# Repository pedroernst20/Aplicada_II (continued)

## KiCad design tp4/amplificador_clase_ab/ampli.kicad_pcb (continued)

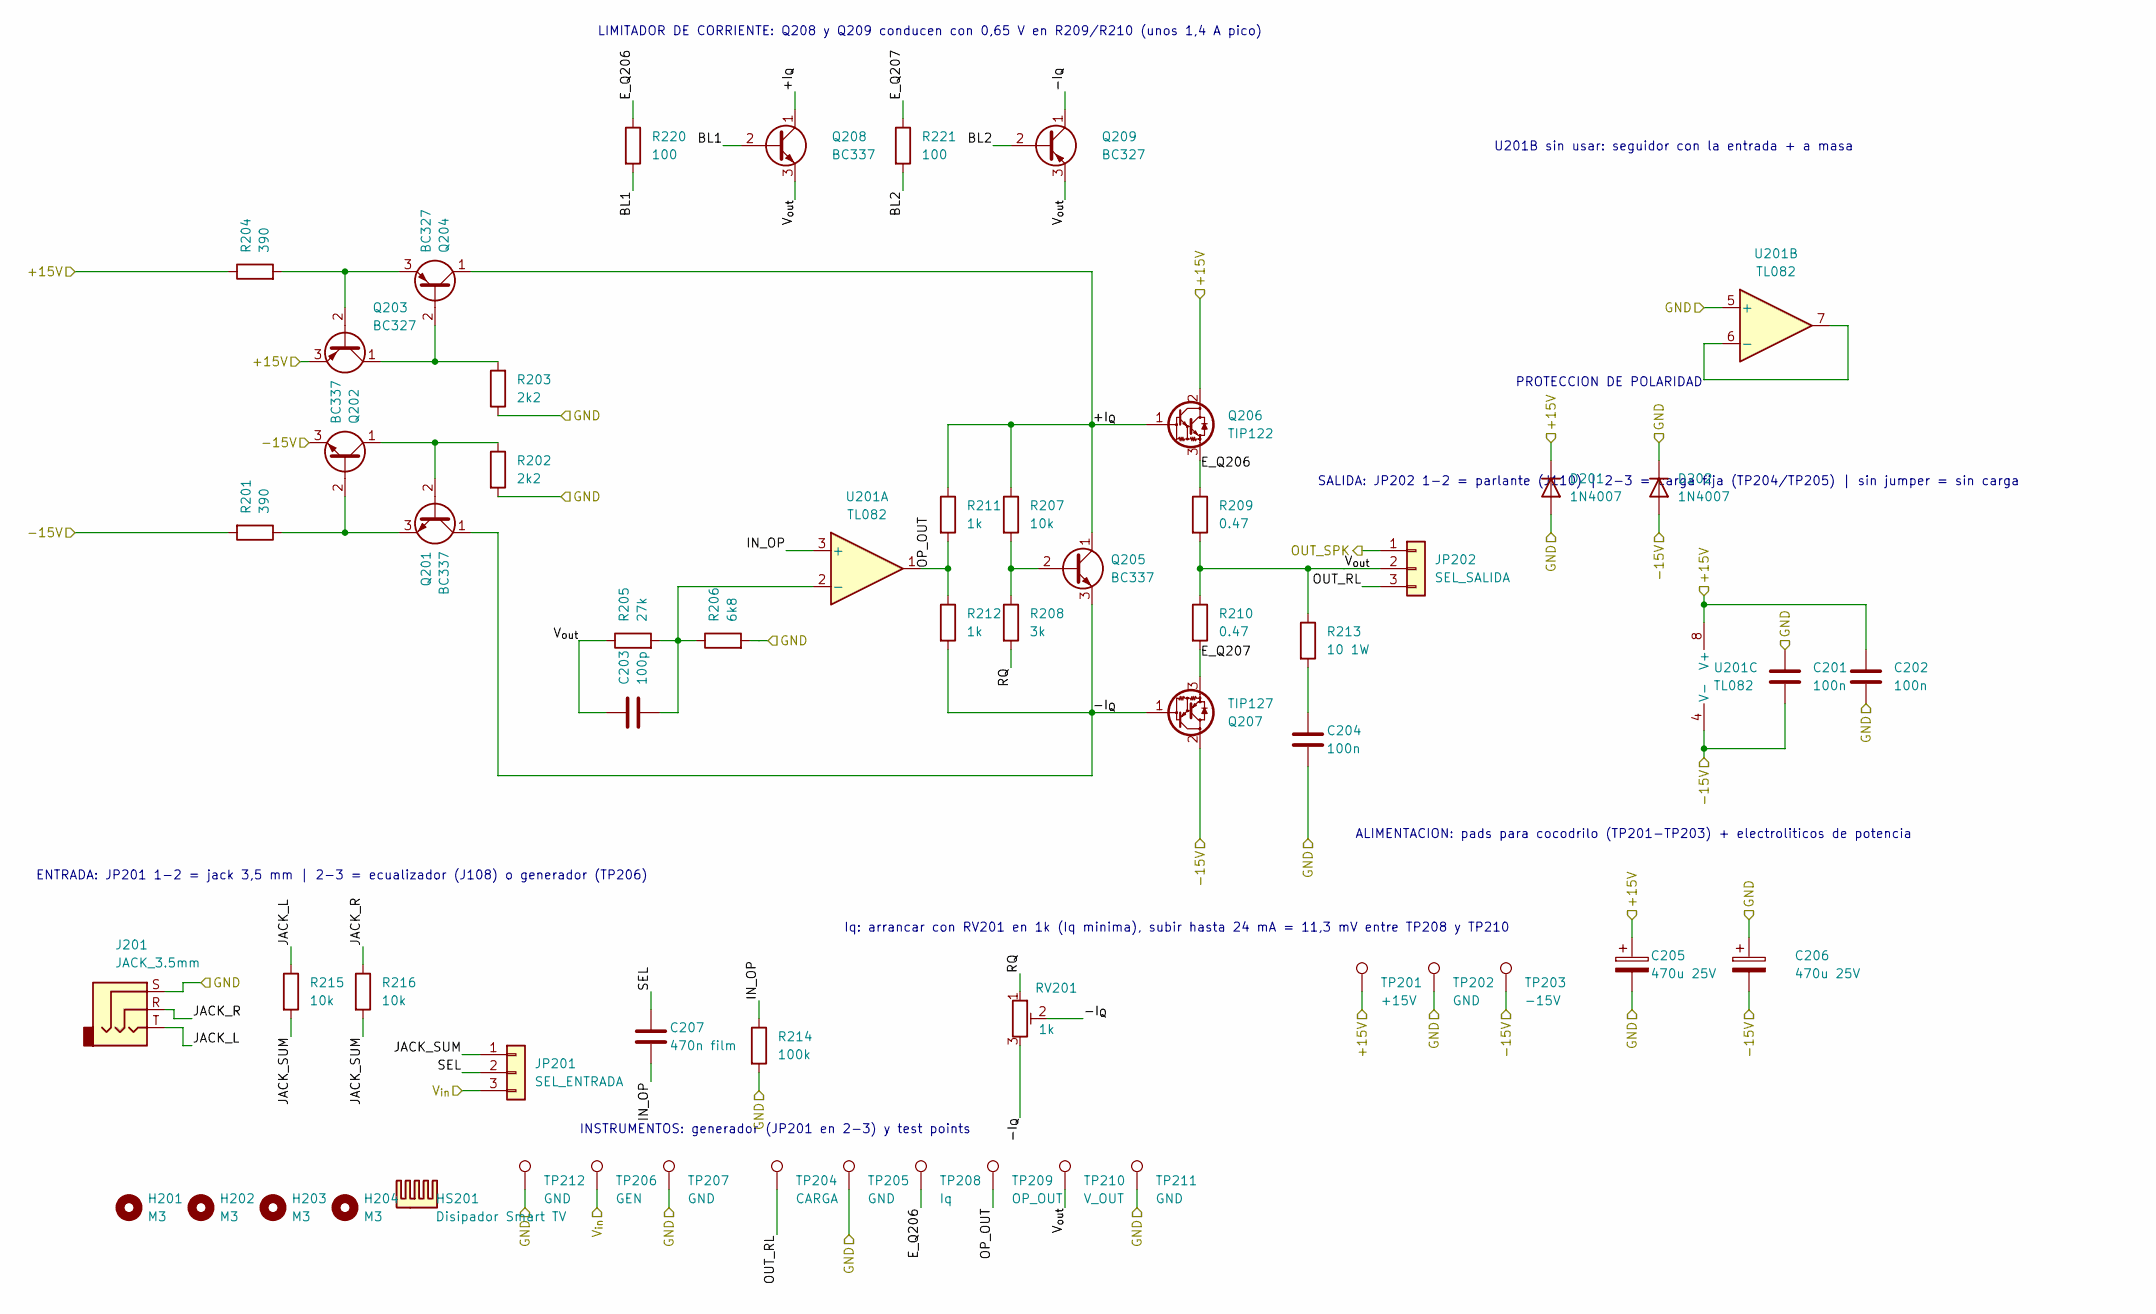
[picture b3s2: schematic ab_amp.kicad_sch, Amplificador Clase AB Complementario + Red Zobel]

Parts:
C201, C202, C204: 100n; C_Rect_L13.0mm_W6.0mm_P10.00mm_FKS3_FKP3_MKS4
C203: 100p; C_Disc_D5.0mm_W2.5mm_P5.00mm
C205, C206: 470u 25V; CP_Radial_D10.0mm_P5.00mm
C207: 470n film; C_Rect_L18.0mm_W7.0mm_P15.00mm_FKS3_FKP3
D201, D202: 1N4007; D_DO-41_SOD81_P10.16mm_Horizontal
H201, H202, H203, H204: M3; MountingHole_3.2mm_M3
HS201: Disipador Smart TV; Disipador_SmartTV_45x45mm
J201: JACK_3.5mm; Jack_3.5mm_Switronic_ST-005-G_horizontal
JP201: SEL_ENTRADA; PinHeader_1x03_P2.54mm_Vertical
JP202: SEL_SALIDA; PinHeader_1x03_P2.54mm_Vertical
Q201, Q202, Q205, Q208: BC337; TO-92_Inline_Wide
Q203, Q204, Q209: BC327; TO-92_Inline_Wide
Q206: TIP122; TO-220-3_Vertical
Q207: TIP127; TO-220-3_Vertical
R201, R204: 390; R_Axial_DIN0207_L6.3mm_D2.5mm_P10.16mm_Horizontal
R202, R203: 2k2; R_Axial_DIN0207_L6.3mm_D2.5mm_P10.16mm_Horizontal
R205: 27k; R_Axial_DIN0207_L6.3mm_D2.5mm_P10.16mm_Horizontal
R206: 6k8; R_Axial_DIN0207_L6.3mm_D2.5mm_P10.16mm_Horizontal
R207, R215, R216: 10k; R_Axial_DIN0207_L6.3mm_D2.5mm_P10.16mm_Horizontal
R208: 3k; R_Axial_DIN0207_L6.3mm_D2.5mm_P10.16mm_Horizontal
R209, R210: 0.47; R_Axial_DIN0516_L15.5mm_D5.0mm_P25.40mm_Horizontal
R211, R212: 1k; R_Axial_DIN0207_L6.3mm_D2.5mm_P10.16mm_Horizontal
R213: 10 1W; R_Axial_DIN0414_L11.9mm_D4.5mm_P15.24mm_Horizontal
R214: 100k; R_Axial_DIN0207_L6.3mm_D2.5mm_P10.16mm_Horizontal
R220, R221: 100; R_Axial_DIN0207_L6.3mm_D2.5mm_P10.16mm_Horizontal
RV201: 1k; Potentiometer_Bourns_3296W_Vertical
TP201: +15V; Pad_Cocodrilo_6x8mm
TP202, TP205, TP207: GND; Pad_Cocodrilo_6x8mm
TP203: -15V; Pad_Cocodrilo_6x8mm
TP204: CARGA; Pad_Cocodrilo_6x8mm
TP206: GEN; Pad_Cocodrilo_6x8mm
TP208: Iq; TP_Puente_P5.08mm
TP209: OP_OUT; TP_Puente_P5.08mm
TP210: V_OUT; TP_Puente_P5.08mm
TP211, TP212: GND; TP_Puente_P5.08mm
U201: TL082; DIP-8_W7.62mm_Socket_LongPads

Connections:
/Amplificador/+15V: C202.1, C205.1, D201.1 (K), Q203.3 (E), Q206.2 (C), R204.1, TP201.1 (1_1), U201.8 (V+); also elsewhere on the board
/Amplificador/+I_{Q}: Q204.1 (C), Q205.1 (C), Q206.1 (B), Q208.1 (C), R207.1, R211.1
/Amplificador/-15V: C201.2, C206.2, D202.2 (A), Q202.3 (E), Q207.2 (C), R201.2, TP203.1 (1_1), U201.4 (V-); also elsewhere on the board
/Amplificador/-I_{Q}: Q201.1 (C), Q205.3 (E), Q207.1 (B), Q209.1 (C), R212.2, RV201.2, RV201.3
/Amplificador/BL1: Q208.2 (B), R220.2
/Amplificador/BL2: Q209.2 (B), R221.2
/Amplificador/E_Q206: Q206.3 (E), R209.1, R220.1, TP208.1 (1_1)
/Amplificador/E_Q207: Q207.3 (E), R210.2, R221.1
/Amplificador/GND: C201.1, C202.2, C204.2, C205.2, C206.1, D201.2 (A), D202.1 (K), J201.S, R202.2, R203.1, R206.2, R214.2, TP202.1 (1_1), TP205.1 (1_1), TP207.1 (1_1), TP211.1, TP212.1, U201.5 (+); also elsewhere on the board
/Amplificador/IN_OP: C207.2, R214.1, U201.3 (+)
/Amplificador/JACK_L: J201.T, R215.1
/Amplificador/JACK_R: J201.R, R216.1
/Amplificador/JACK_SUM: JP201.1, R215.2, R216.2
/Amplificador/OP_OUT: R211.2, R212.1, TP209.1 (1_1), U201.1
/Amplificador/OUT_RL: JP202.3, TP204.1 (1_1)
/Amplificador/OUT_SPK: JP202.1; also elsewhere on the board
/Amplificador/RQ: R208.2, RV201.1
/Amplificador/SEL: C207.1, JP201.2
/Amplificador/V_{in}: JP201.3, TP206.1 (1_1); also elsewhere on the board
/Amplificador/V_{out}: C203.1, JP202.2, Q208.3 (E), Q209.3 (E), R205.1, R209.2, R210.1, R213.1, TP210.1
unnamed: C204.1, R213.2
unnamed: Q201.2 (B), Q202.1 (C), R202.1
unnamed: Q201.3 (E), Q202.2 (B), R201.1
unnamed: Q203.2 (B), Q204.3 (E), R204.2
unnamed: Q203.1 (C), Q204.2 (B), R203.2
unnamed: Q205.2 (B), R207.2, R208.1
unnamed: C203.2, R205.2, R206.1, U201.2 (-)
unnamed: U201.6 (-), U201.7

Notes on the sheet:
ENTRADA: JP201 1-2 = jack 3,5 mm | 2-3 = ecualizador (J108) o generador (TP206)
Iq: arrancar con RV201 en 1k (Iq minima), subir hasta 24 mA = 11,3 mV entre TP208 y TP210
ALIMENTACION: pads para cocodrilo (TP201-TP203) + electroliticos de potencia
U201B sin usar: seguidor con la entrada + a masa
LIMITADOR DE CORRIENTE: Q208 y Q209 conducen con 0,65 V en R209/R210 (unos 1,4 A pico)
PROTECCION DE POLARIDAD
INSTRUMENTOS: generador (JP201 en 2-3) y test points
SALIDA: JP202 1-2 = parlante (J110) | 2-3 = carga fija (TP204/TP205) | sin jumper = sin carga

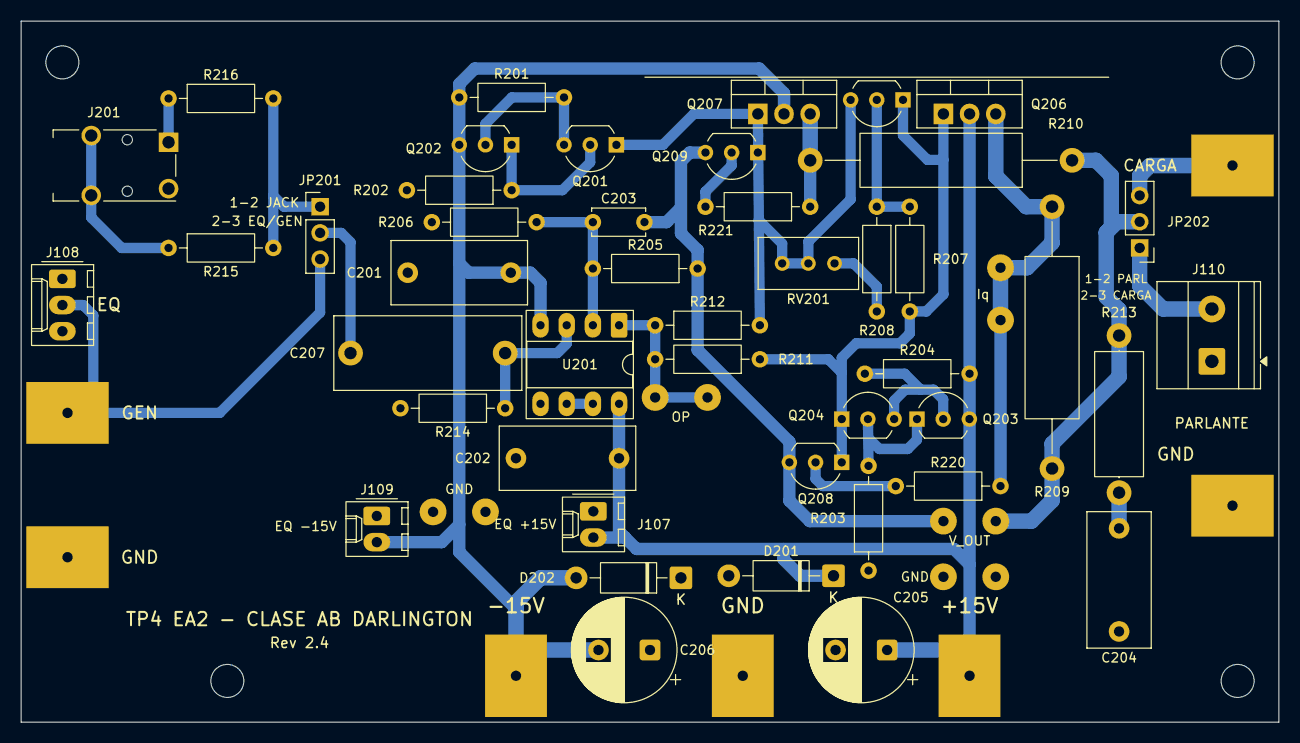
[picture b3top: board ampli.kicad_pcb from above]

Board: 2 copper layers, 122.0 x 68.0 mm, 62 parts (0 on the bottom side), 28 nets.

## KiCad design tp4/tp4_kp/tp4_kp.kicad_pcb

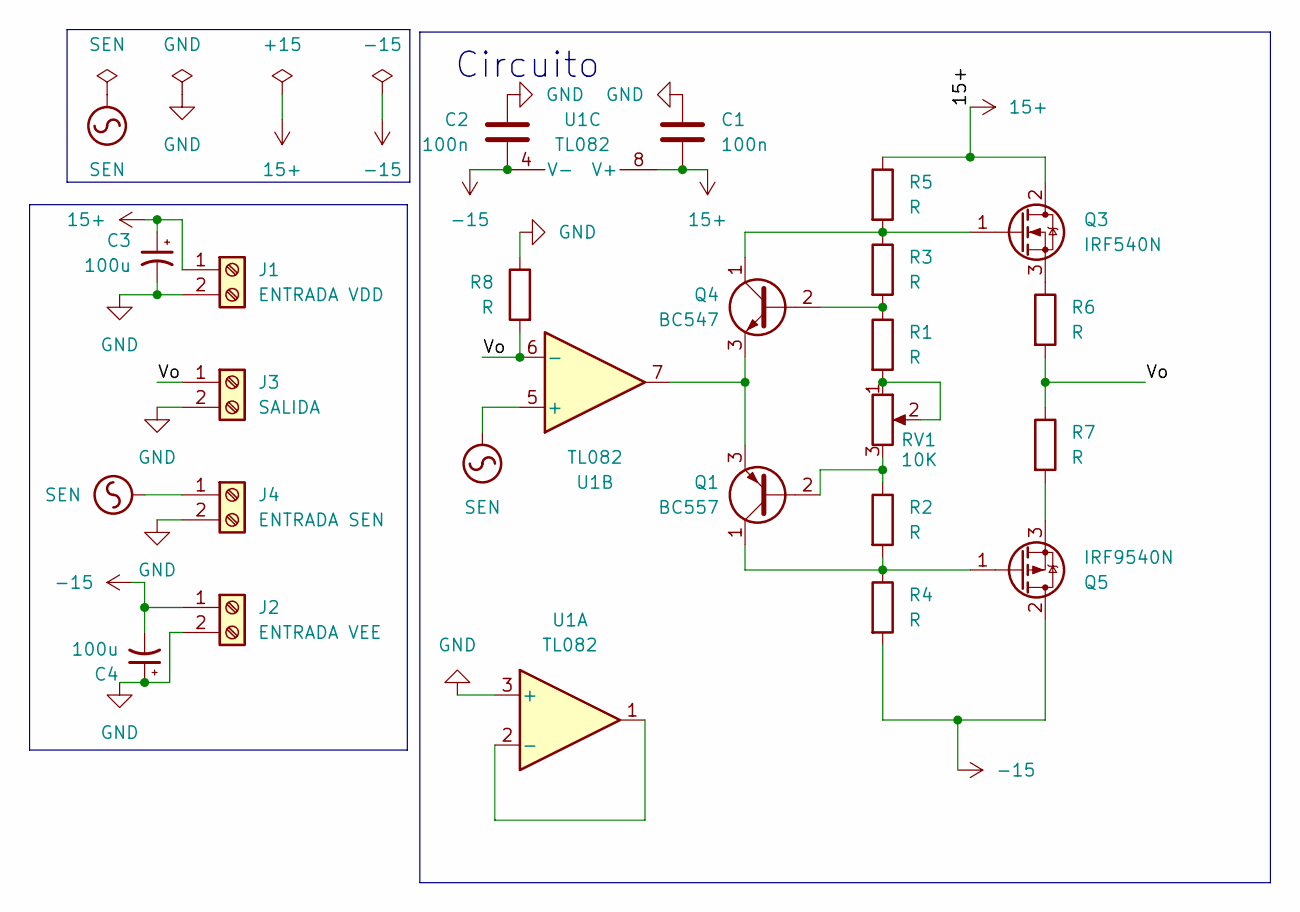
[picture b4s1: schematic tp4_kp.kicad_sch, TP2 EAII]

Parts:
C1, C2: 100n; C_Disc_D5.0mm_W2.5mm_P5.00mm
C3, C4: 100u; CP_Radial_D4.0mm_P2.00mm
J1: ENTRADA VDD; TerminalBlock_Phoenix_MKDS-1,5-2-5.08_1x02_P5.08mm_Horizont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
J2: ENTRADA VEE; TerminalBlock_Phoenix_MKDS-1,5-2-5.08_1x02_P5.08mm_Horizont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
J3: SALIDA; TerminalBlock_Phoenix_MKDS-1,5-2-5.08_1x02_P5.08mm_Horizont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
J4: ENTRADA SEN; TerminalBlock_Phoenix_MKDS-1,5-2-5.08_1x02_P5.08mm_Horizont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
Q1: BC557; TO-92_Inline
Q3: IRF540N; TO-220-3_Vertical
Q4: BC547; TO-92_Inline
Q5: IRF9540N; TO-220-3_Vertical
R1, R2, R3, R4, R5, R8: R; R_Axial_DIN0207_L6.3mm_D2.5mm_P10.16mm_Horizontal
R6, R7: R; R_Axial_DIN0411_L9.9mm_D3.6mm_P15.24mm_Horizontal
RV1: 10K; Potentiometer_Bourns_3296W_Vertical
U1: TL082; DIP-8_W7.62mm_Socket_LongPads

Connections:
15+: C1.2, C3.1, J1.1, Q3.2 (D), R5.1, U1.8 (V+)
-15: C2.2, C4.2, J2.1, Q5.2 (D), R4.2, U1.4 (V-)
/Vo: J3.1, R6.2, R7.1, R8.2, U1.6 (-)
GND: C1.1, C2.1, C3.2, C4.1, J1.2, J2.2, J3.2, J4.2, R8.1, U1.3 (+)
unnamed: Q1.2 (B), R2.1, RV1.3
unnamed: Q1.1 (C), Q5.1 (G), R2.2, R4.1
unnamed: Q1.3 (E), Q4.3 (E), U1.7
unnamed: Q3.1 (G), Q4.1 (C), R3.1, R5.2
unnamed: Q3.3 (S), R6.1
unnamed: Q4.2 (B), R1.1, R3.2
unnamed: Q5.3 (S), R7.2
unnamed: R1.2, RV1.1, RV1.2
unnamed: U1.1, U1.2 (-)
SEN: J4.1, U1.5 (+)

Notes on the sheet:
Circuito

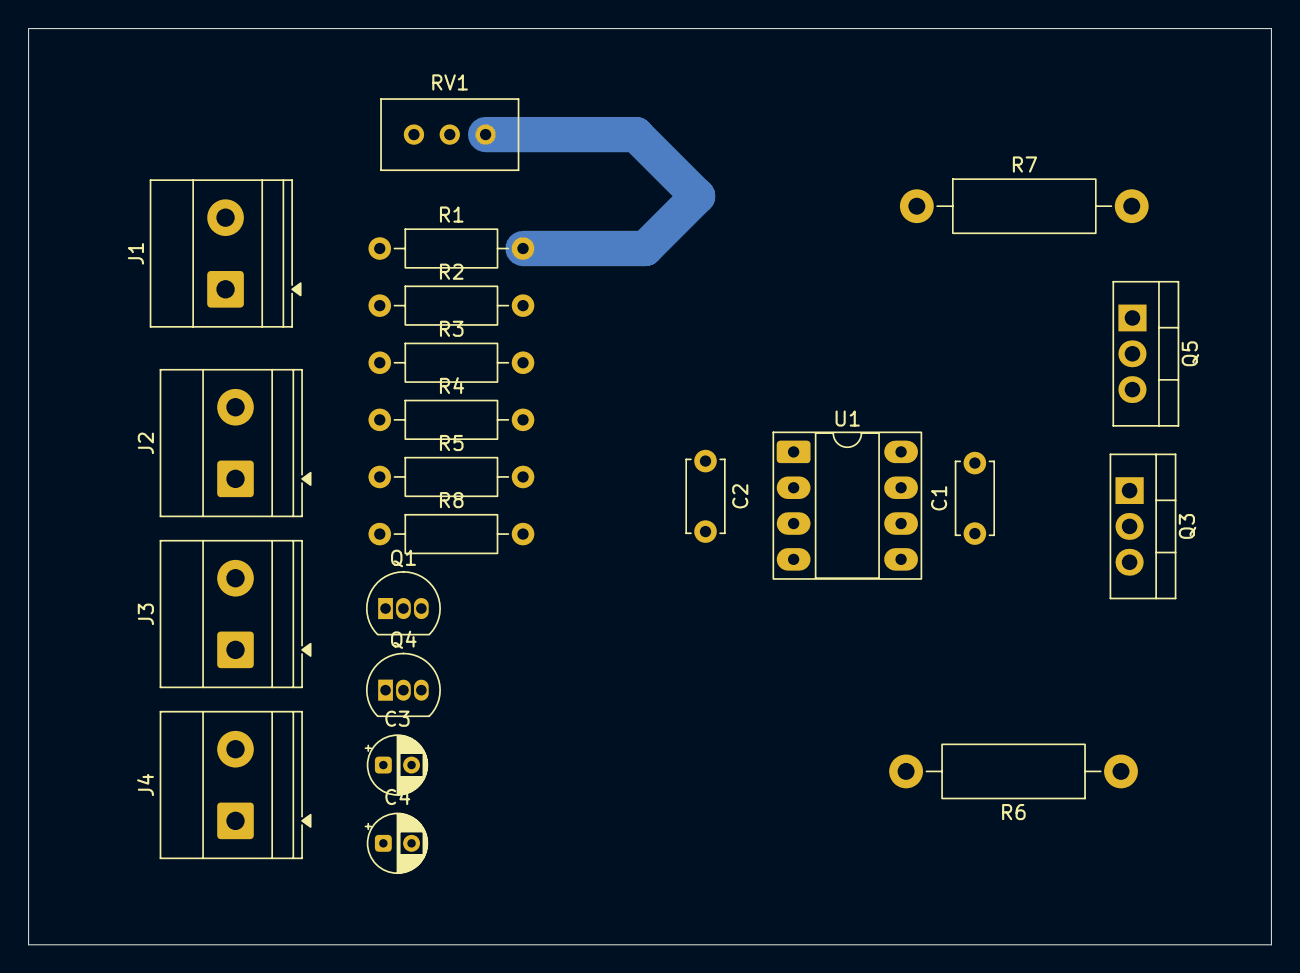
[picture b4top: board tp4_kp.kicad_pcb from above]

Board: 2 copper layers, 88.1 x 65.0 mm, 22 parts (0 on the bottom side), 14 nets.

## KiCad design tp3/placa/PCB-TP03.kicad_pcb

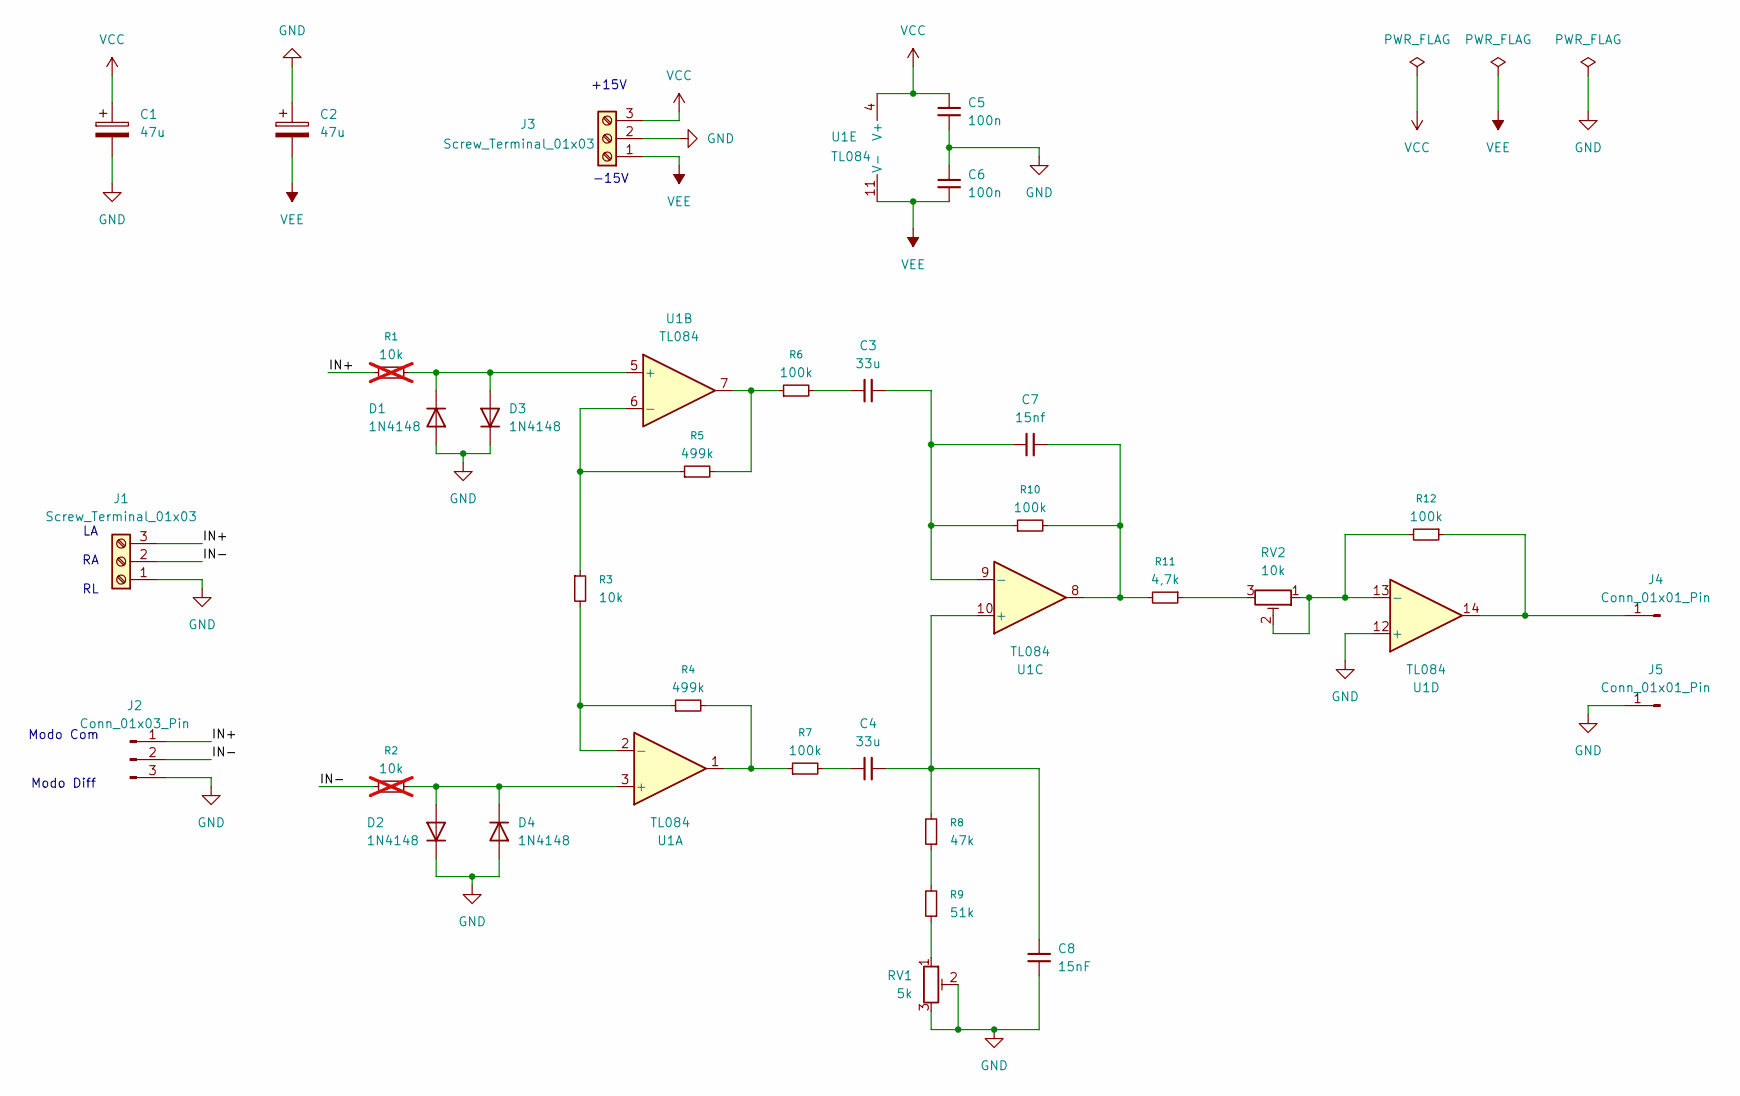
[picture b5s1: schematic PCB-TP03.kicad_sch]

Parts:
C1, C2: 47u; CP_Radial_D5.0mm_P2.50mm
C3, C4: 33u; CP_Radial_Tantal_D5.0mm_P2.50mm
C5, C6: 100n; C_0805_2012Metric_Pad1.18x1.45mm_HandSolder
C7: 15nf; C_Rect_L7.0mm_W3.5mm_P5.00mm
C8: 15nF; C_Rect_L7.0mm_W3.5mm_P5.00mm
D1, D2, D3, D4: 1N4148; D_DO-35_SOD27_P7.62mm_Horizontal
J1, J3: Screw_Terminal_01x03; TerminalBlock_Phoenix_MKDS-1,5-3_1x03_P5.00mm_Horizontal
J2: Conn_01x03_Pin; PinHeader_1x03_P2.54mm_Vertical
J4, J5: Conn_01x01_Pin; PinHeader_1x01_P2.54mm_Vertical
R1, R2: 10k; R_Axial_DIN0207_L6.3mm_D2.5mm_P10.16mm_Horizontal; not fitted
R3: 10k; R_Axial_DIN0207_L6.3mm_D2.5mm_P10.16mm_Horizontal
R4, R5: 499k; R_Axial_DIN0207_L6.3mm_D2.5mm_P10.16mm_Horizontal
R6, R7, R10, R12: 100k; R_Axial_DIN0207_L6.3mm_D2.5mm_P10.16mm_Horizontal
R8: 47k; R_Axial_DIN0207_L6.3mm_D2.5mm_P10.16mm_Horizontal
R9: 51k; R_Axial_DIN0207_L6.3mm_D2.5mm_P10.16mm_Horizontal
R11: 4,7k; R_Axial_DIN0207_L6.3mm_D2.5mm_P10.16mm_Horizontal
RV1: 5k; Potentiometer_Bourns_3296W_Vertical
RV2: 10k; Potentiometer_Bourns_3296W_Vertical
U1: TL084; DIP-14_W7.62mm_Socket_LongPads

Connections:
/IN+: J1.3, J2.1, R1.1
/IN-: J1.2, J2.2, R2.1
GND: C1.2, C2.1, C5.2, C6.1, C8.1, D1.2 (A), D2.1 (K), D3.1 (K), D4.2 (A), J1.1, J2.3, J3.2, J5.1 (Pin_1_1), RV1.2, RV1.3, U1.12 (+)
unnamed: C3.1, R6.2
unnamed: C4.1, R7.2
unnamed: C7.2, R10.2, R11.2, U1.8
unnamed: D1.1 (K), D3.2 (A), R1.2, U1.5 (+)
unnamed: D2.2 (A), D4.1 (K), R2.2, U1.3 (+)
unnamed: J4.1 (Pin_1_1), R12.1, U1.14
unnamed: R4.2, R7.1, U1.1
unnamed: R5.2, R6.1, U1.7
unnamed: R8.1, R9.2
unnamed: R9.1, RV1.1
unnamed: R11.1, RV2.3
unnamed: R3.2, R4.1, U1.2 (-)
unnamed: R3.1, R5.1, U1.6 (-)
unnamed: C4.2, C8.2, R8.2, U1.10 (+)
unnamed: C3.2, C7.1, R10.1, U1.9 (-)
unnamed: R12.2, RV2.1, RV2.2, U1.13 (-)
VCC: C1.1, C5.1, J3.3, U1.4 (V+)
VEE: C2.2, C6.2, J3.1, U1.11 (V-)

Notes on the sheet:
Modo Diff
+15V
-15V
Modo Com
LA RA RL

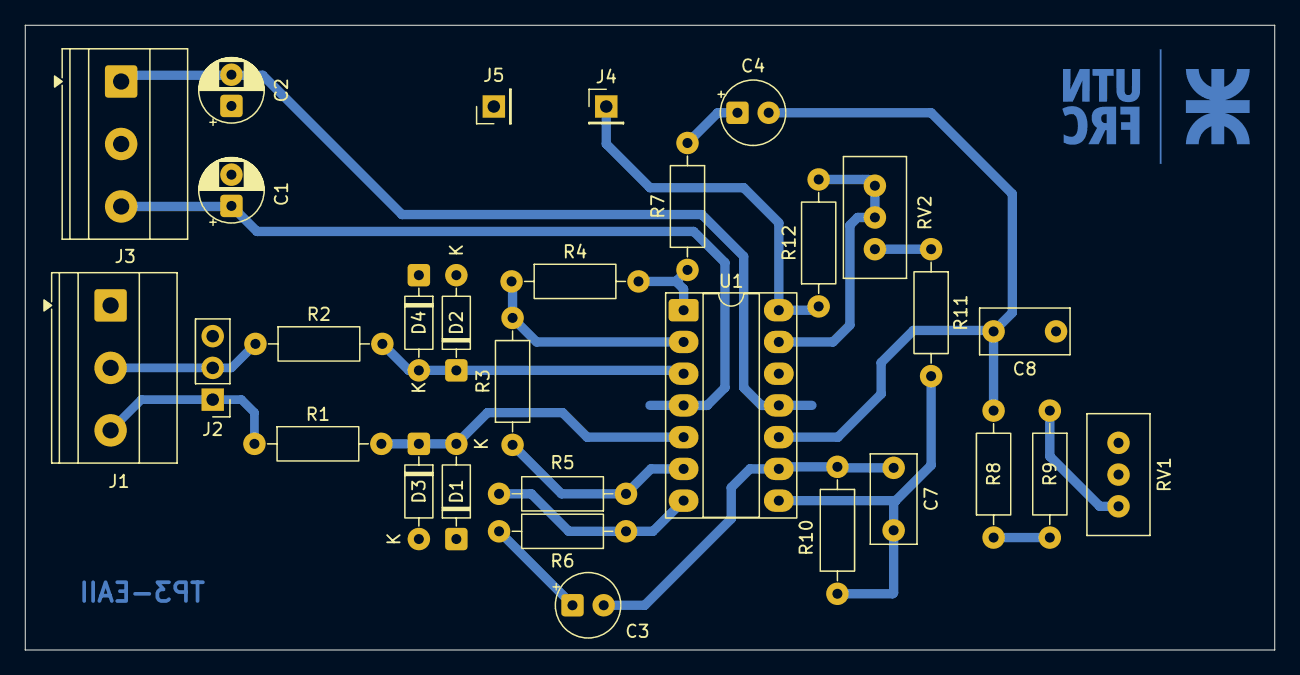
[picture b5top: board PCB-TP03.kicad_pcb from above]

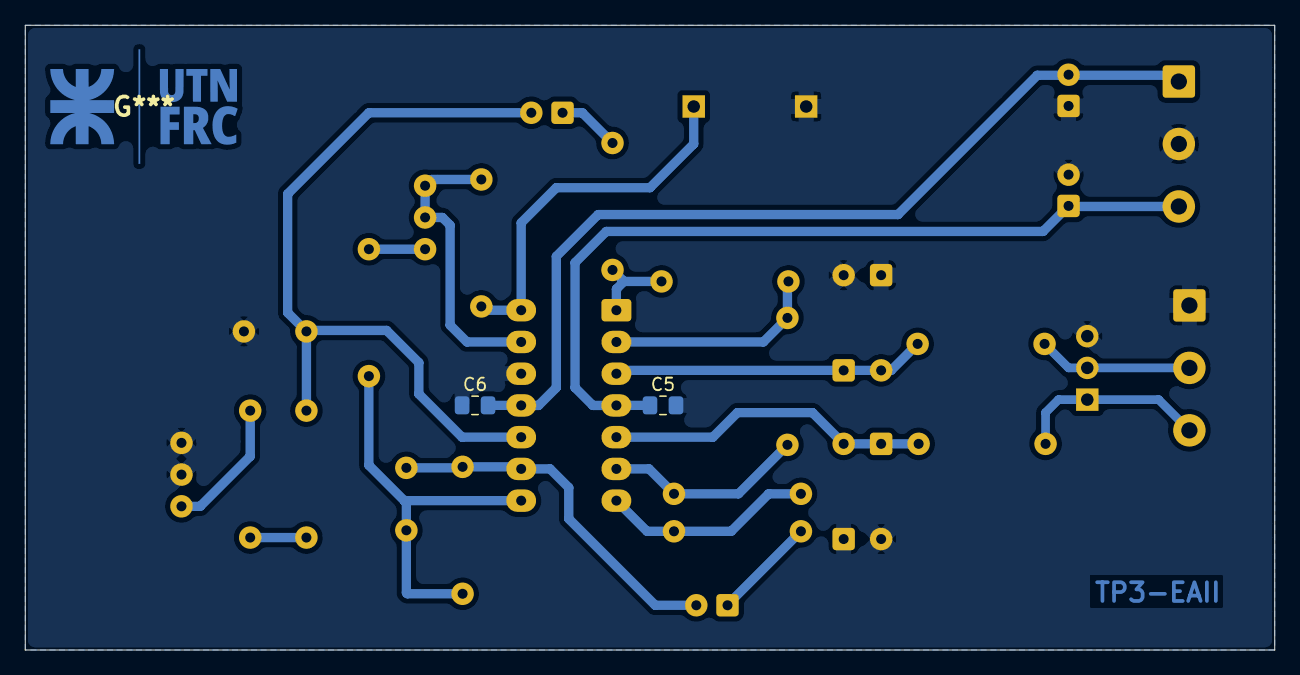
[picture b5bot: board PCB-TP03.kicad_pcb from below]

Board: 2 copper layers, 100.0 x 50.0 mm, 32 parts (2 on the bottom side), 21 nets.

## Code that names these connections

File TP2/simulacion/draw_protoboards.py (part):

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    draw_resistor(ax, col_x, 'B', 6, 'RAIL_GND_L', 6, num_rows=30, label="R32: 1k")
    draw_wire(ax, col_x, 'D', 6, 'C', 20, num_rows=30, color="#8E24AA", lw=2.0, arc=0.2, label="Vref1 (+1.5V)")
    draw_resistor(ax, col_x, 'D', 20, 'D', 21, num_rows=30, label="R5: 100k")
    draw_test_point(ax, col_x, 'A', 21, num_rows=30, label="TEST Offset\n(Pin 7)", color="#8E24AA", side='left')
    
    # 5. Stage 3: Miller Integrator (U1C)
    draw_wire(ax, col_x, 'G', 19, 'RAIL_GND_R', 19, num_rows=30, color="#212121", lw=2.2, label="GND")
    draw_resistor(ax, col_x, 'C', 21, 'G', 20, num_rows=30, label="R8: 10k")
    draw_cap_ceramic(ax, col_x, 'H', 20, 'H', 21, num_rows=30, label="C1: 10nF")
    draw_resistor(ax, col_x, 'I', 20, 'I', 21, num_rows=30, label="R9: 100k")
    draw_test_point(ax, col_x, 'J', 21, num_rows=30, label="TEST Pre_int\n(Pin 8)", color="#F57C00", side='right')
    
    # 6. Stage 4: Centering S2 (U1D)
    draw_resistor(ax, col_x, 'G', 21, 'G', 17, num_rows=30, label="R6: 100k")
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    # Feedback R11 // C3
    draw_resistor(ax, col_x, 'B', 15, 'B', 16, num_rows=30, label="R11: 62k")
    draw_cap_ceramic(ax, col_x, 'A', 15, 'A', 16, num_rows=30, label="C3: 56pF")
    draw_test_point(ax, col_x, 'D', 15, num_rows=30, label="TEST Pre_der\n(Pin 1)", color="#7B1FA2", side='left')
    
    # 4. Stage 6: Signal 3 Conditioning (U2B)
    draw_resistor(ax, col_x, 'C', 15, 'C', 19, num_rows=30, label="R27: 200k")
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
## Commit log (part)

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2026-04-15 Archivos de simulacion y valores de Vin y Vout
2026-04-16 Tabla respuesta en frecuencia
2026-04-26 agrega archivos tp1 y tp2
2026-04-28 agrega sim tp2
2026-04-30 avance pcb y fin de sim
2026-05-06 resistencias normalizadas y div r, footprints
2026-05-27 version final pcb
